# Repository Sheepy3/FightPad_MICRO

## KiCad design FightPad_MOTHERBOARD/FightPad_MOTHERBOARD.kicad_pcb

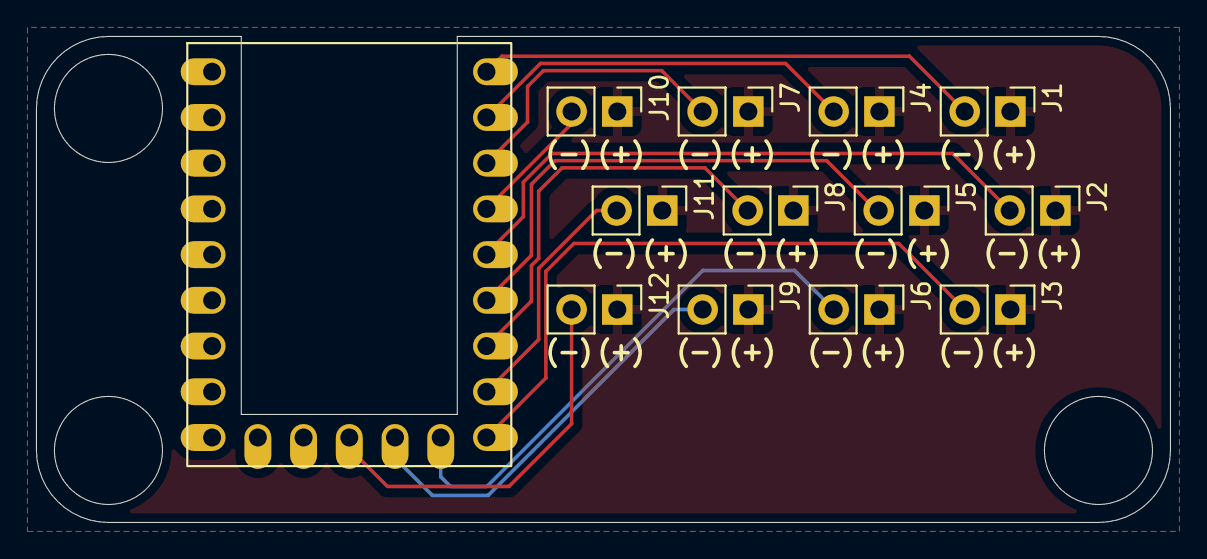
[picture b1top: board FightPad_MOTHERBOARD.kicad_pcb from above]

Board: 2 copper layers, 63.0 x 27.0 mm, 13 parts (0 on the bottom side), 13 nets.

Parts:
J1, J2, J3, J4, J5, J6, J7, J8, J9, J10, J11, J12: Conn_01x02_Socket; PinHeader_1x02_P2.54mm_Vertical
U1: rp2040-zero; rp2040-zero-tht

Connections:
A: J1.2, U1.1 (0)
B: J4.2, U1.2 (1)
C: J7.2, U1.3 (2)
D: J10.2, U1.4 (3)
E: J2.2, U1.5 (4)
F: J5.2, U1.6 (5)
G: J8.2, U1.7 (6)
GND: J1.1, J2.1, J3.1, J4.1, J5.1, J6.1, J7.1, J8.1, J9.1, J10.1, J11.1, J12.1
H: J11.2, U1.8 (7)
I: J3.2, U1.9 (8)
J: J6.2, U1.10 (9)
K: J9.2, U1.11 (10)
L: J12.2, U1.12 (11)

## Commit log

2024-09-08 init commit of pcbs
